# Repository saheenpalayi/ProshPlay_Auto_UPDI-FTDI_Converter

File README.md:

# ProshPlay_Auto_UPDI-FTDI_Converter
At last I found the circuit that I'm looking for to make my own automatic FTDI and UPDI converter
## Overview
I've been trying to make an unified programer for the AVR series 1 and Series 2 microcontrollers which uses the single UPDI pin for programming. and we can create the UPDI programer by adding a simple resistor to an existing USB to FTDI or UART converter available in the market. but that to read serial we need another FTDI or we need to switch the converter and the programer board back in forth while programming  

## Schematic

## PCB Layout

## 3D PCB 

## Reference
-

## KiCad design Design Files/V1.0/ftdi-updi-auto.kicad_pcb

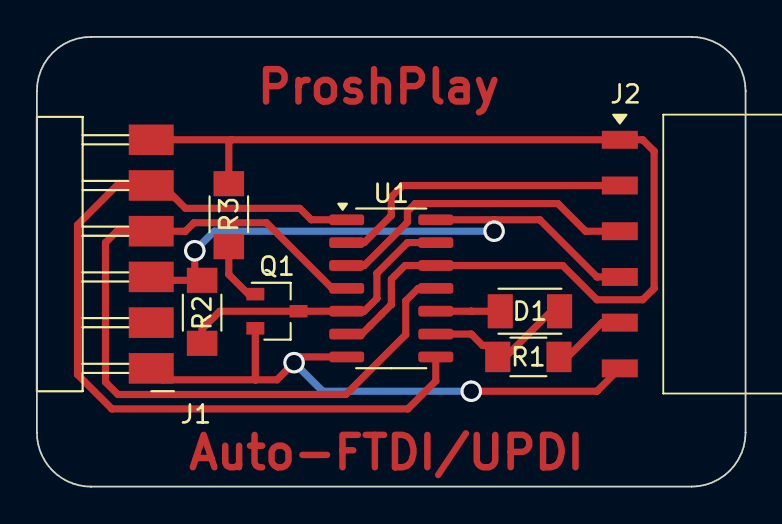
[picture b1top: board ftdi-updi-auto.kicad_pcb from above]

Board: 2 copper layers, 39.4 x 25.0 mm, 8 parts (0 on the bottom side), 12 nets.

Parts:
D1: Diode_Schottky_MiniSMA
J1: Conn_PinHeader_FTDI_1x06_P2.54mm_Horizontal_SMD; PinHeader_1x06_P2.54mm_Horizontal_SMD
J2: Conn_PinSocket_FTDI_1x06_P2.54mm_Horizontal_SMD; PinSocket_1x06_P2.54mm_Horizontal_SMD
Q1: Transistor_MOSFET_NCh_SOT23; SOT-23-3
R1, R2, R3: R_1206
U1: HEF4066BT; SOIC-14_3.9x8.7mm_P1.27mm

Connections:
DTR: J1.6, J2.1, R3.2, U1.6 (3E), U1.12 (4E)
GND: J1.1, J2.6, Q1.2 (S), U1.7 (VSS)
MODE-FTDI: Q1.3 (D), R2.1, U1.5 (2E), U1.13 (1E)
unnamed: D1.2 (A), R1.1, U1.9 (3Z)
unnamed: D1.1 (K), U1.10 (4Z)
unnamed: Q1.1 (G), R3.1
RX: J1.5, U1.1 (1Y), U1.8 (3Y)
RX-T: J2.2, U1.2 (1Z)
TX: J1.4, U1.4 (2Y), U1.11 (4Y)
TX-T: J2.3, U1.3 (2Z)
UPDI: J2.5, R1.2
VCC: J1.3, J2.4, R2.2, U1.14 (VDD)

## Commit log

2025-05-14 added files of v1 and v2
